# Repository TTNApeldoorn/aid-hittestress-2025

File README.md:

# aid-hittestress-2025

These climate sensors are designed for the LIFE-IP Climate adaption project in Apeldoorn. The sensors measures temperature, humidity and air quality.
The sensors are mounted in lampposts and communicate via LoRAWan with the TTN network.

## Requirements 
- The sensor measures each 2.5 minutes temperatue, humidity and particular matter PM1.0, 2.5 and 10
- The sensor sends the measurements to the TTN network using LoRaWan radio
- The sensor can be mounted on lamppost (case IP65)
- The sensor operates on LiPo battery (for minimal 18 hours) and can be charged by 230V supply 
- The sensor battery is charged at night by the lamppost
- GPS location and battery voltage are reported at regular intervals

## Realization

 Climate Sensor in Kradex housing

Air inlet particle sensor, with insect sreen

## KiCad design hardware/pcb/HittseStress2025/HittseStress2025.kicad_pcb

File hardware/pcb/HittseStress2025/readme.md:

# HittseStress2025 PCB Design

This directory contains the KiCad project files for the HittseStress2025 printed circuit board (PCB). This PCB is designed to interface the TTGO T-Beam ESP32 LoRa module with the SPS30 particulate matter sensor and other components for the climate sensor system.

## Contents

- `HittseStress2025.kicad_pcb` - PCB layout file
- `HittseStress2025.kicad_sch` - Schematic file
- `HittseStress2025.kicad_pro` - KiCad project file
- `gerbers/` - Gerber files for PCB manufacturing
- `my-KiCad-library/` - Custom KiCad symbols and footprints
- `HittseStress2025-backups/` - Automatic backup files

## Purpose

The PCB serves as a shield/breakout board that provides:
- Power management connections
- Interface connections for the SPS30 particulate matter sensor
- Proper pin routing for the ESP32-based TTGO T-Beam module
- Support for battery charging and power supply from the lamppost

This board enables the climate sensor to be mounted in lampposts and operate on battery power with charging capability.

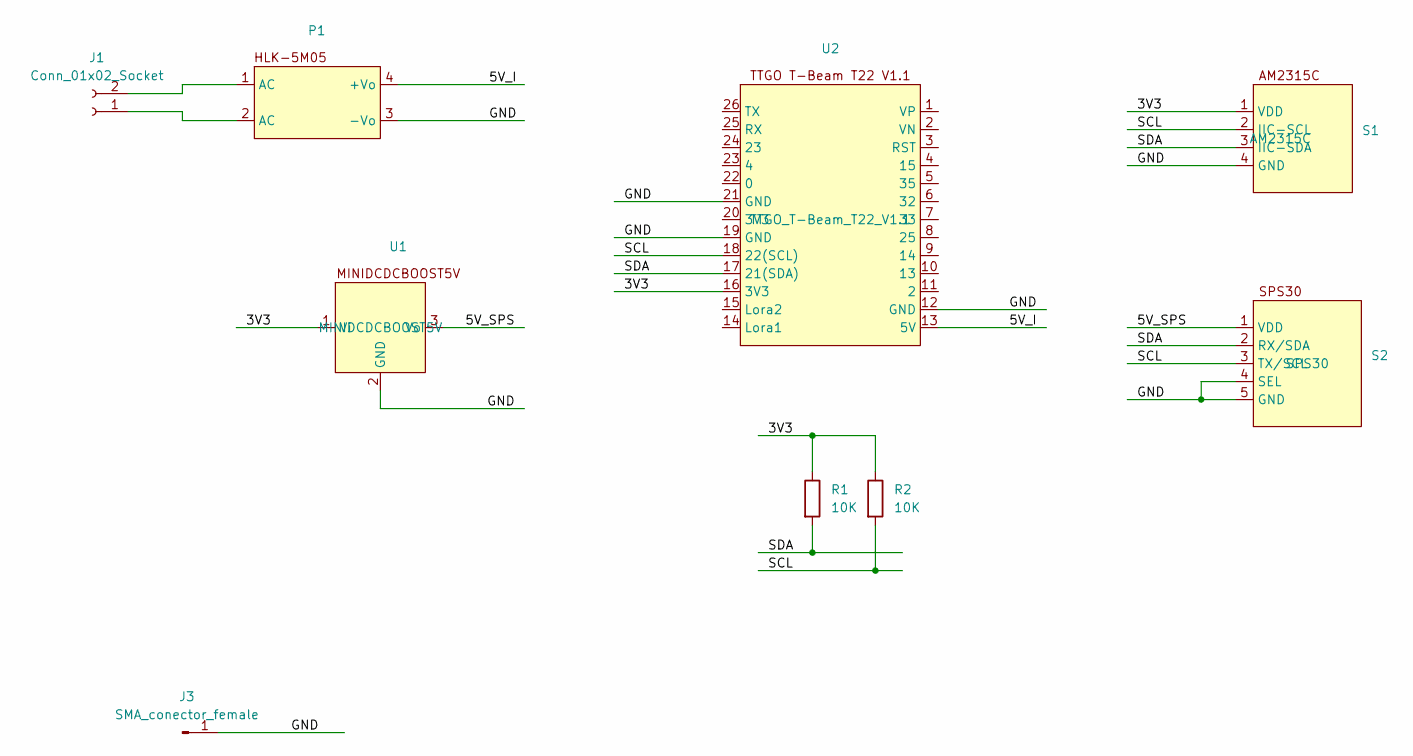
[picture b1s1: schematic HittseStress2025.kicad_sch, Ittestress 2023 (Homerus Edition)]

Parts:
J1: Conn_01x02_Socket; PhoenixContact_MCV_1,5_2-G-5.08_1x02_P5.08mm_Vertical
J3: SMA_conector_female; SMA-ANT-CONN
P1: HLK-5M05
R1, R2: 10K; R_Axial_DIN0309_L9.0mm_D3.2mm_P12.70mm_Horizontal
S1: AM2315C
S2: SPS30
U1: MINIDCDCBOOST5V
U2: TTGO_T-Beam_T22_V1.1

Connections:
/3V3: R1.1, R2.1, S1.1 (VDD), U1.1 (Vi), U2.16 (3V3)
/5V_I: P1.4 (+Vo), U2.13 (5V)
/5V_SPS: S2.1 (VDD), U1.3 (Vo)
/GND: J3.1, P1.3 (-Vo), S1.4 (GND), S2.4 (SEL), S2.5 (GND), U1.2 (GND), U2.12 (GND), U2.19 (GND), U2.21 (GND)
/SCL: R2.2, S1.2 (IIC-SCL), S2.3 (TX/SCL), U2.18 (22(SCL))
/SDA: R1.2, S1.3 (IIC-SDA), S2.2 (RX/SDA), U2.17 (21(SDA))
unnamed: J1.1, P1.2 (AC)
unnamed: J1.2, P1.1 (AC)

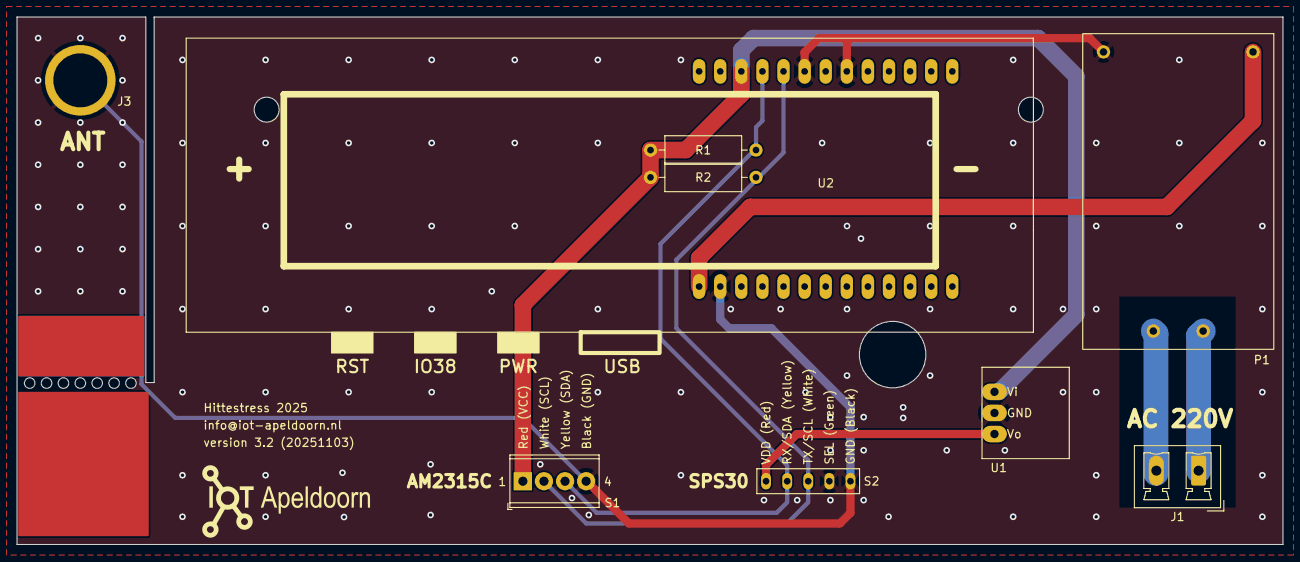
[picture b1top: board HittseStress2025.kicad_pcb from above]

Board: 2 copper layers, 152.4 x 63.5 mm, 9 parts (0 on the bottom side), 8 nets.

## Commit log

2025-09-22 Add files via upload
    initial code
2025-09-23 Add files via upload
    test version 4
2025-09-23 Delete software/src/LoRaBoards.cpp
    replaced by pmu.cpp
2025-09-23 Delete software/src/LoRaBoards.h
    replaced by pmu.h
2025-09-23 Update README.md
    typos
2025-10-07 Added PCB design to be adapted/updated
2025-10-07 Added workbench
2025-10-13 Updated to version 2025 for use with LilyGO T-Beam V1.2
2025-11-03 Corrected position of components
2025-11-21 send status frequency changed main.cpp
2025-11-23 Added documentation on housing
2025-11-24 Added hittestress2025_SPS_omhulsel_TPU.stl and updated documentation
